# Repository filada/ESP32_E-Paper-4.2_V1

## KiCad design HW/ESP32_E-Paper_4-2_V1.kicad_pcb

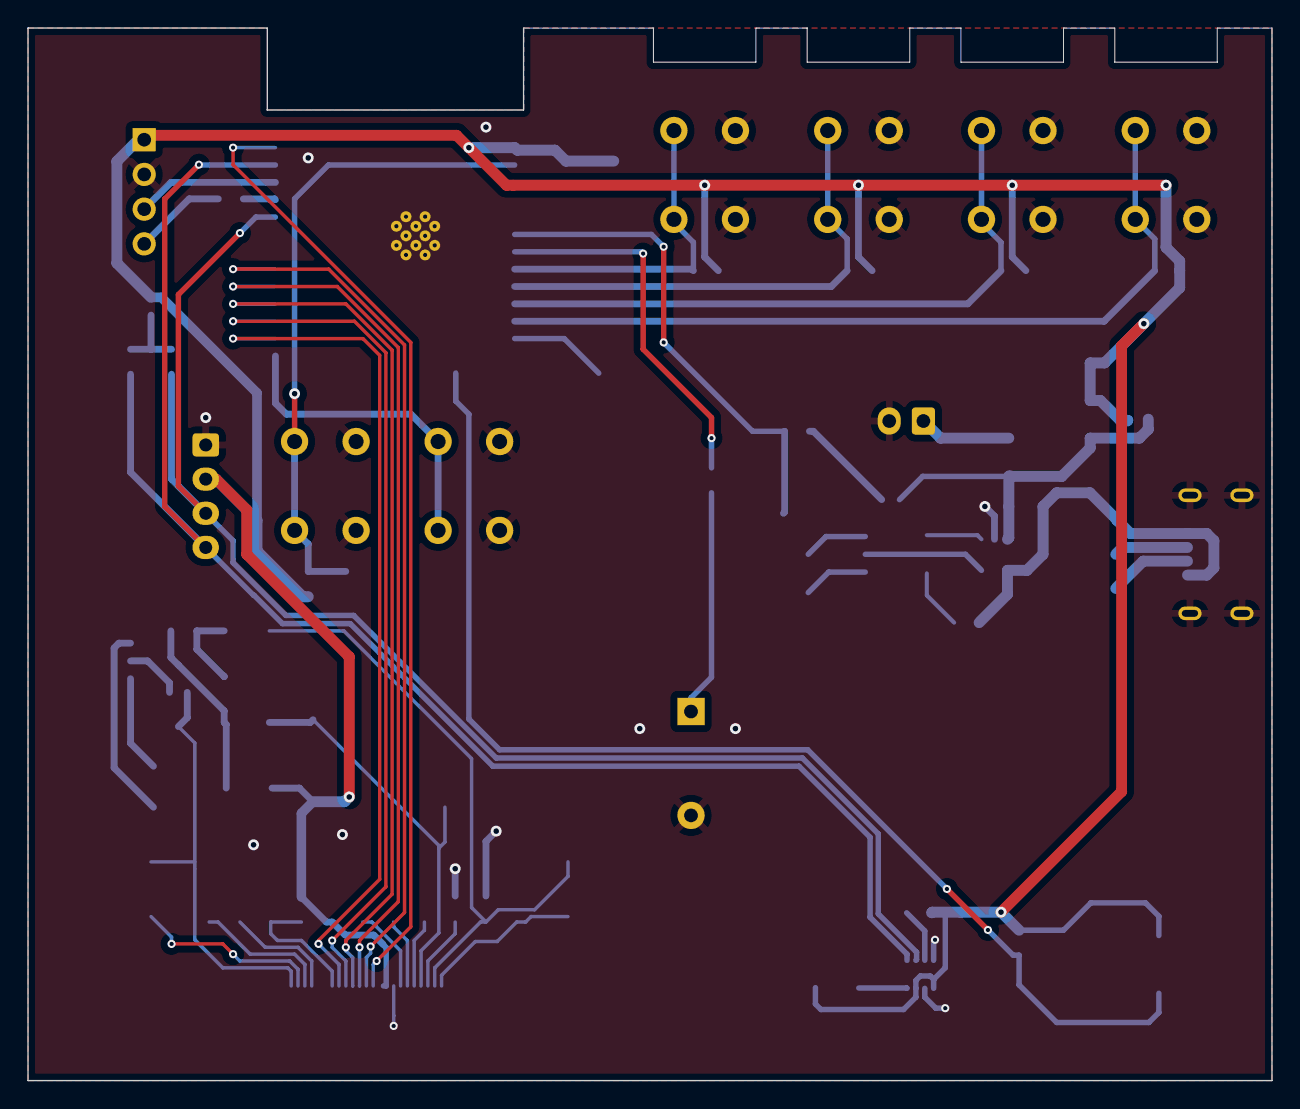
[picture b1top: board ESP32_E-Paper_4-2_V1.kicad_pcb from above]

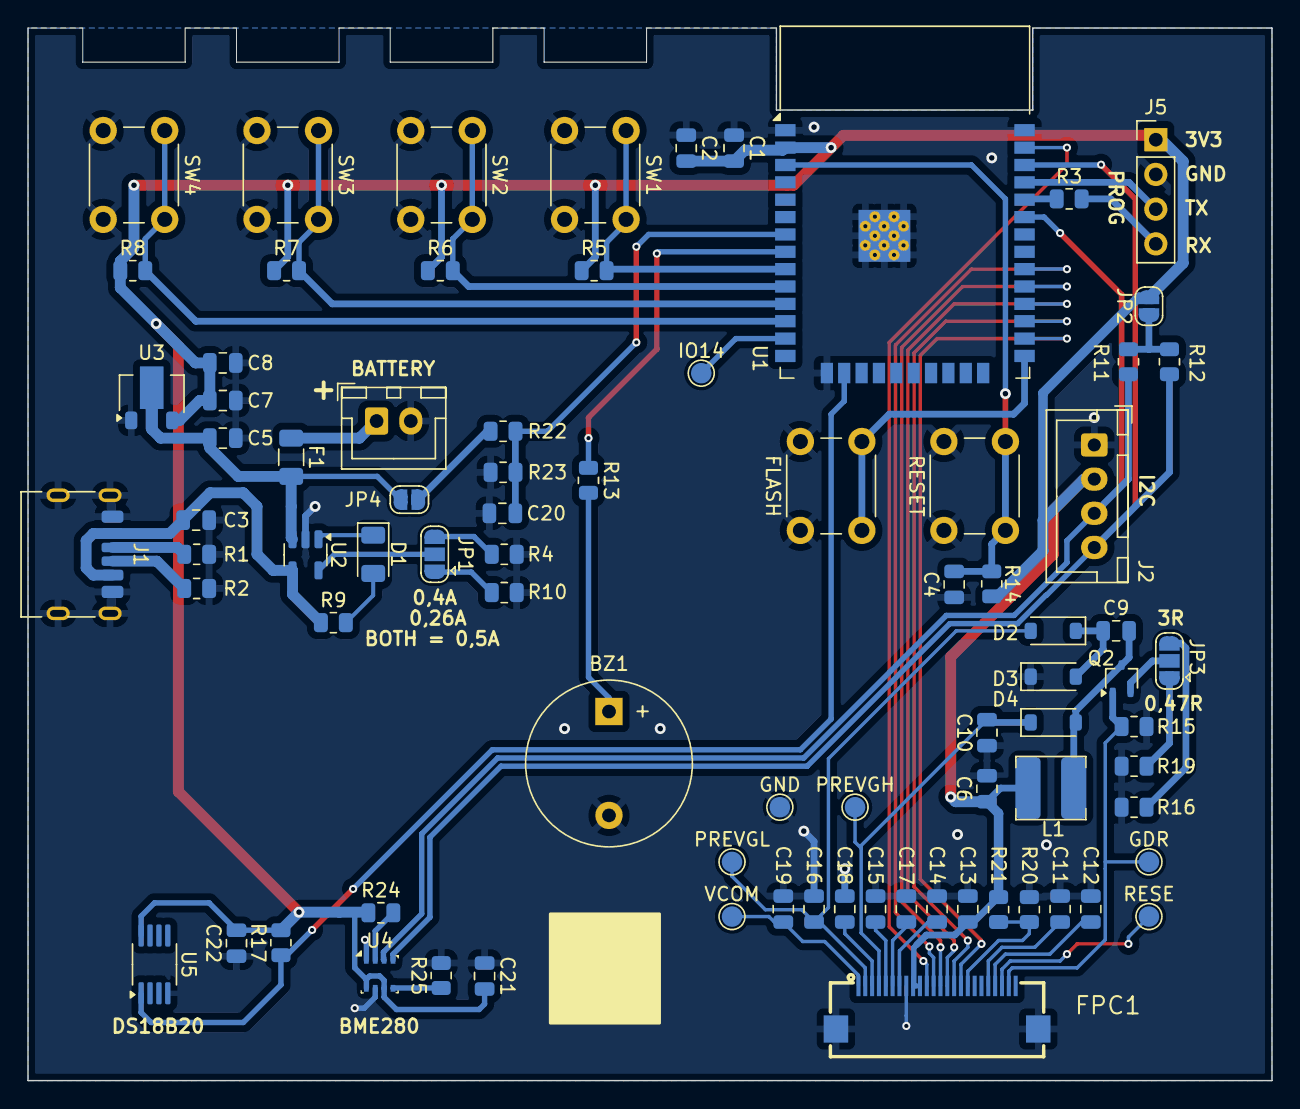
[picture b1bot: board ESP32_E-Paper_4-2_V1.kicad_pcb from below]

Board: 2 copper layers, 91.0 x 77.0 mm, 81 parts (81 on the bottom side), 55 nets.

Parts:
BZ1: Piezo; Buzzer_12x9.5RM7.6
C1, C3, C5, C8: 10uF; C_0805_2012Metric
C2, C4, C7, C20, C21, C22: 100nF; C_0805_2012Metric
C6, C9, C10, C11, C12, C15, C16, C18: 4.7uF; C_0805_2012Metric
C13, C14, C17, C19: 1uF; C_0805_2012Metric
D1: CHARGING; LED_1206_3216Metric
D2, D3, D4: MBR0530; D_SOD-123
F1: 1A; Fuse_1206_3216Metric
FLASH: FLASH; SW_PUSH_6mm_H7.3mm
FPC1: FPC_E-Paper; JUSHUO AFC24-S24FIC-00
GDR: GDR; TestPoint_Pad_D1.5mm
GND: GND; TestPoint_Pad_D1.5mm
IO14: IO14; TestPoint_Pad_D1.5mm
J1: USB_C_Receptacle_PowerOnly_6P; USB_C_Receptacle_HRO_TYPE-C-31-M-17
J2: I2C; JST_XH_B4B-XH-A_1x04_P2.50mm_Vertical
J3: BATTERY; JST_XH_B2B-XH-A_1x02_P2.50mm_Vertical
J5: PROG; PinHeader_1x04_P2.54mm_Vertical
JP1: CH_CURRENT; SolderJumper-3_P1.3mm_Open_RoundedPad1.0x1.5mm
JP2: I2C_PULLUPS; SolderJumper-2_P1.3mm_Open_RoundedPad1.0x1.5mm
JP3: RES_SEL; SolderJumper-3_P1.3mm_Open_RoundedPad1.0x1.5mm
JP4: ADC-BAT; SolderJumper-2_P1.3mm_Open_RoundedPad1.0x1.5mm
L1: 10uH/1A; inductor_4.5x4_V1
PREVGH: PREVGH; TestPoint_Pad_D1.5mm
PREVGL: PREVGL; TestPoint_Pad_D1.5mm
Q2: Si1308EDL; SOT-323_SC-70
R1, R2: 5K1; R_0805_2012Metric
R3: 470R; R_0805_2012Metric
R4: 1K65; R_0805_2012Metric
R5, R6, R7, R8, R11, R12, R14, R15, R21, R24, R25: 10K; R_0805_2012Metric
R9: 1K; R_0805_2012Metric
R10: 3K3; R_0805_2012Metric
R13: 100R; R_0805_2012Metric
R16, R20: 3R; R_0805_2012Metric
R17: 4K7; R_0805_2012Metric
R19: 0.47R; R_0805_2012Metric
R22: 1M; R_0805_2012Metric
R23: 1M3; R_0805_2012Metric
RESE: RESE; TestPoint_Pad_D1.5mm
RESET: RESET; SW_PUSH_6mm_H7.3mm
SW1, SW2, SW3, SW4: BTN1; SW_PUSH_6mm_H7.3mm
U1: ESP32-WROOM-32E; ESP32-WROOM-32D
U2: TP4054; TSOT-23-5
U3: MCP1700x-330xxMB; SOT-89-3
U4: BME280; Bosch_LGA-8_2.5x2.5mm_P0.65mm_ClockwisePinNumbering
U5: DS18B20U; MSOP-8_3x3mm_P0.65mm
VCOM: VCOM; TestPoint_Pad_D1.5mm

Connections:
+3V3: C1.2, C2.2, C6.1, C7.1, C8.1, C13.1, C21.2, C22.2, FPC1.9, FPC1.10, J2.2, J5.1, JP2.2 (B), L1.1, R5.1, R6.1, R7.1, R8.1, R14.1, R17.2, R21.1, R24.1, U1.2 (VDD), U3.3 (VO), U4.6 (VDDIO), U4.8 (VDD), U5.8 (V_{DD})
+BATT: C5.1, F1.2, JP4.1 (A), U2.3 (BAT), U3.2 (VI)
/BS: FPC1.17, R20.2, R21.2
/BTN1: R5.2, SW1.1, U1.9 (IO33)
/BTN2: R6.2, SW2.1, U1.10 (IO25)
/BTN3: R7.2, SW3.1, U1.11 (IO26)
/BTN4: R8.2, SW4.1, U1.12 (IO27)
/BUSY: FPC1.16, U1.26 (IO4)
/CS: FPC1.13, U1.29 (IO5)
/D/C: FPC1.14, U1.28 (IO17)
/EN: C4.2, R14.2, RESET.2, U1.3 (EN)
/GDR: FPC1.23, GDR.1, Q2.1 (G), R15.1
/IO0: FLASH.2, U1.25 (IO0)
/IO13: R17.1, U1.16 (IO13), U5.1 (DQ)
/IO14: IO14.1, U1.13 (IO14)
/PIEZO: R13.1, U1.8 (IO32)
/PREVGH: C10.1, D4.1 (K), FPC1.4, PREVGH.1
/PREVGL: C16.1, D2.2 (A), FPC1.2, PREVGL.1
/RES: FPC1.15, U1.27 (IO16)
/RESE: FPC1.22, RESE.1
/RX: J5.4, R3.2
/SCL: J2.4, R12.1, U1.36 (IO22), U4.4 (SCK)
/SCLK: FPC1.12, U1.30 (IO18)
/SDA: J2.3, R11.1, U1.33 (IO21), U4.3 (SDI)
/SDI: FPC1.11, U1.37 (IO23)
/TX: J5.3, U1.35 (TXD0/IO1)
/VBAT_ADC: C20.1, R22.2, R23.1, U1.7 (IO35)
/VCOM: C19.1, FPC1.1, VCOM.1
GND: BZ1.2 (-), C1.1, C2.1, C3.2, C4.1, C5.2, C6.2, C7.2, C8.2, C10.2, C11.2, C12.2, C13.2, C14.2, C15.2, C16.2, C17.2, C18.2, C19.2, C20.2, C21.1, C22.1, D3.1 (K), FLASH.1, FPC1.8, FPC1.25, FPC1.26, GND.1, J1.A12 (GND), J1.B12 (GND), J1.S1 (SHIELD), J2.1, J3.2, J5.2, R1.2, R2.1, R4.2, R10.2, R15.2, R16.2, R19.2, R20.1, R23.2, R25.2, RESET.1, SW1.2, SW2.2, SW3.2, SW4.2, U1.1 (GND), U1.15 (GND), U1.38 (GND), U1.39 (GND), U2.2 (GND), U3.1 (GND), U4.1 (GND), U4.7 (GND), U5.4 (GND)
unnamed: BZ1.1 (+), R13.2
unnamed: C11.1, FPC1.20
unnamed: C12.1, FPC1.21
unnamed: C14.1, FPC1.7
unnamed: C15.1, FPC1.5
unnamed: C17.1, FPC1.6
unnamed: C18.1, FPC1.3
unnamed: D1.2 (A), R9.2
unnamed: D1.1 (K), U2.1 (~CHRG)
unnamed: C9.1, D2.1 (K), D3.2 (A)
unnamed: C9.2, D4.2 (A), L1.2, Q2.3 (D)
unnamed: J1.A5 (CC1), R1.1
unnamed: J1.B5 (CC2), R2.2
unnamed: F1.1, J3.1
unnamed: JP1.1 (A), R10.1
unnamed: JP1.3 (B), R4.1
unnamed: JP1.2 (C), U2.5 (PROG)
unnamed: JP2.1 (A), R11.2, R12.2
unnamed: JP3.1 (A), R19.1
unnamed: JP3.3 (B), R16.1
unnamed: JP3.2 (C), Q2.2 (S)
unnamed: JP4.2 (B), R22.1
unnamed: R3.1, U1.34 (RXD0/IO3)
unnamed: C3.1, J1.A9 (VBUS), J1.B9 (VBUS), R9.1, U2.4 (V_{CC})
unnamed: R24.2, U4.2 (CSB)
unnamed: R25.1, U4.5 (SDO)

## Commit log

2025-05-28 first commit
    SCH and PCB design done
